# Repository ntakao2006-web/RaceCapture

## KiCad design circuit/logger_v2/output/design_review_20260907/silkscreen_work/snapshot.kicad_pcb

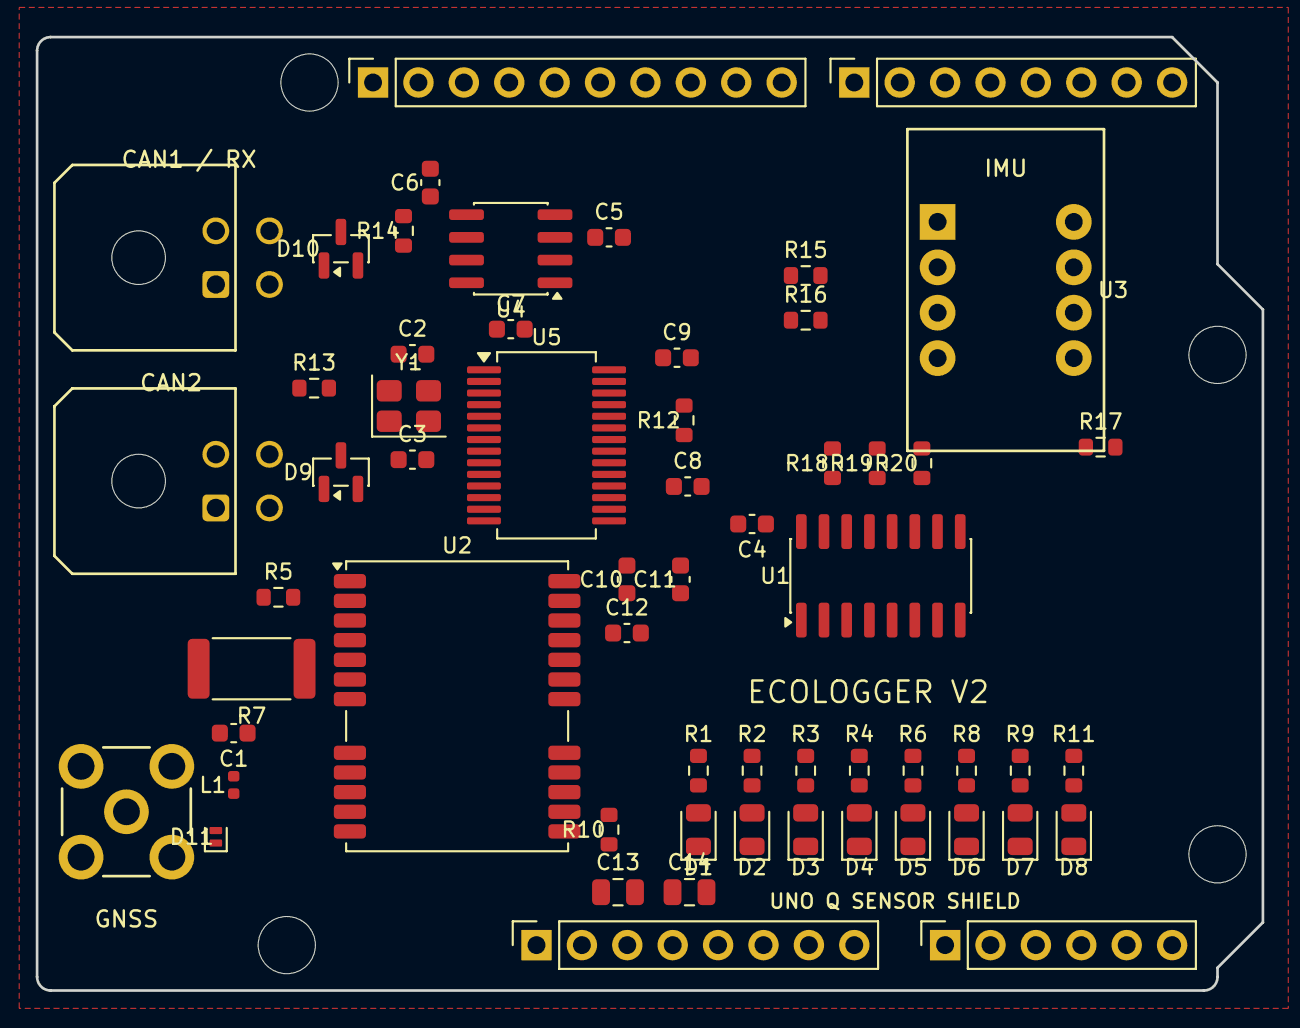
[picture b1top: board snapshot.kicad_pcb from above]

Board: 2 copper layers, 68.6 x 53.3 mm, 63 parts (0 on the bottom side), 46 nets, no tracks yet.

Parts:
C1, C4, C5, C6, C7, C8, C9, C10, C12: 100nF; C_0603_1608Metric
C2, C3: 18pF; C_0603_1608Metric
C11: 1uF; C_0603_1608Metric
C13, C14: 10uF; C_0805_2012Metric
D1, D2, D3, D4, D5, D6, D7, D8: GREEN 0805; LED_0805_2012Metric
D9, D10: NUP2105LT1G; SOT-23
D11: RF ESD; D_SOD-882
J1: S-037-TGG; SMA_S-037-TGG_Horizontal
J2: Digital/PWM; PinSocket_1x10_P2.54mm_Vertical
J3: Power; PinSocket_1x08_P2.54mm_Vertical
J4: Analog; PinSocket_1x06_P2.54mm_Vertical
J5: Digital/PWM; PinSocket_1x08_P2.54mm_Vertical
J6, J7: 43045-0400; Molex_Micro-Fit_3.0_43045-0400_2x02_P3.00mm_Horizontal
L1: 27nH; L_0402_1005Metric
MH1, MH2, MH3, MH4: MountingHole_3.2mm
R1, R2, R3, R4, R6, R8, R9, R11: 680R; R_0603_1608Metric
R5, R10, R12, R17: 10k; R_0603_1608Metric
R7: 22R 1W; R_2512_6332Metric
R13, R14: 120; R_0603_1608Metric
R15, R16: 4.7k; R_0603_1608Metric
R18, R19, R20: 47k; R_0603_1608Metric
U1: 74HC595D,118; SOIC-16_3.9x9.9mm_P1.27mm
U2: NEO-M9N-00B; ublox_NEO
U3: BNO055_module; AE_BNO055_BO
U4: ATA6561-GAQW-N; SOIC-8_3.9x4.9mm_P1.27mm
U5: MCP25625-E/SS; SSOP-28_5.3x10.2mm_P0.65mm
Y1: 20MHz 12pF; Crystal_SMD_3225-4Pin_3.2x2.5mm

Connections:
+3V3: C4.1, C6.1, C7.1, C8.1, C10.1, C11.1, C12.1, C13.1, J3.4, R5.1, R12.1, R15.2, R16.2, R17.1, U1.10, U1.16, U2.22, U2.23, U3.1, U4.1, U4.5, U5.1, U5.19
+5V: C5.1, C9.1, C14.1, J3.5, J6.1, U4.3, U5.27
/CAN1_RXD: J5.3, U4.4
/CAN2_CS_N: J2.8, R12.2, U5.17
/CAN2_INT_N: J2.9, U5.13
/CAN2_RESET_N: J2.10, R17.2, U5.18
/GNSS_PPS: J5.2, U2.3
/GNSS_RESET_N: J5.5, R5.2, U2.8
/GNSS_RF: D11.2, J1.1, L1.1, U2.11
/GNSS_RXD: J5.7, U2.21
/GNSS_TXD: J5.8, U2.20
/IMU_RESET_N: J5.6, U3.5
/IMU_SCL: J2.1, R15.1, U3.4
/IMU_SDA: J2.2, R16.1, U3.3
/SPI2_MISO: J2.6, U5.16
/SPI2_MOSI: J2.7, R18.1, U1.14, U5.15
/SPI2_SCK: J2.5, R19.1, U1.11, U5.14
/STATUS_LATCH: J5.1, R20.1, U1.12
GND: C1.2, C2.2, C3.2, C4.2, C5.2, C6.2, C7.2, C8.2, C9.2, C10.2, C11.2, C12.2, C13.2, C14.2, D1.1, D2.1, D3.1, D4.1, D5.1, D6.1, D7.1, D8.1, D9.3, D10.3, D11.1, J1.2, J2.4, J3.6, J3.7, J6.4, J7.4, R10.2, R18.2, R19.2, R20.2, U1.8, U1.13, U2.7, U2.10, U2.12, U2.13, U2.24, U3.2, U3.7, U4.2, U4.8, U5.5, U5.10, U5.26, Y1.2, Y1.4
unnamed: C1.1, L1.2, R7.2
unnamed: D1.2, R1.2
unnamed: D2.2, R2.2
unnamed: D3.2, R3.2
unnamed: D4.2, R4.2
unnamed: D5.2, R6.2
unnamed: D6.2, R8.2
unnamed: D7.2, R9.2
unnamed: D8.2, R11.2
unnamed: D9.1, J6.2, R13.2, U5.4
unnamed: D9.2, J6.3, R13.1, U5.3
unnamed: D10.1, J7.2, R14.2, U4.7
unnamed: D10.2, J7.3, R14.1, U4.6
unnamed: R1.1, U1.15
unnamed: R2.1, U1.1
unnamed: R3.1, U1.2
unnamed: R4.1, U1.3
unnamed: R6.1, U1.4
unnamed: R8.1, U1.5
unnamed: R9.1, U1.6
unnamed: R11.1, U1.7
unnamed: R10.1, U2.14
unnamed: R7.1, U2.9
unnamed: C2.1, U5.9, Y1.3
unnamed: C3.1, U5.8, Y1.1
unnamed: U5.21, U5.28
unnamed: U5.20, U5.24

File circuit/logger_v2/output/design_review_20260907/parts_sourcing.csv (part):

"Reference","Existing_part","Proposed_part","Manufacturer","LCSC","JLC_library","JLC_assembly","Package","Stock_reported","Stock_evidence","Checked_JST","Status","URL","Notes"
"U1","TC74HC595AF","74HC595D,118","Nexperia","C5947","Basic","Economic and Standard","SOIC-16 3.9mm","302263","JLC indexed page snapshot","2026-09-07","Selected final design","https://jlcpcb.com/partdetail/Nexperia-74HC595D118/C5947","Change footprint from 5.3mm SOP; same logic pinout"
"U2","NEO-M9N-00B","NEO-M9N-00B","u-blox","C5119087","Extended","Standard Only","SMD-24P","500","JLC indexed page snapshot; current page confirms Standard Only","2026-09-07","Selected final design","https://jlcpcb.com/partdetail/UBLOX-NEO_M9N00B/C5119087","LCSC separately showed 322; do not confuse supplier stock with allocated PCBA stock"
"U3","AE-BNO055-BO","AE-BNO055-BO","Akizuki","","Unconfirmed","Excluded from SMT BOM/CPL; post-assembly","18x11mm module","TBD","No exact JLC registration verified","2026-09-07","Selected post-assembly","https://akizukidenshi.com/catalog/g/g116996/","Use module-specific BOM; never assign bare BNO055 C93216 to this footprint"
"U3 alternative","AE-BNO055-BO","BNO055","Bosch Sensortec","C93216","Extended","Standard Only","LGA-28 5.2x3.8mm","8957","JLC category indexed stock snapshot","2026-09-07","Alternative only","https://jlcpcb.com/partdetail/BoschSensortec-BNO055/C93216","Requires full circuit redesign around same sensor IC and axis validation"
"U4","ATA6561-GAQW-N","ATA6561-GAQW","Microchip","C2929602","Extended","SMT listed; service class not displayed","SOIC-8","1117","LCSC stock only; JLC quantity not displayed","2026-09-07","Selected final design","https://jlcpcb.com/partdetail/MicrochipTech-ATA6561GAQW/C2929602","AEC-Q100 version instead of industrial -N; confirm ordering allocation"
"U5","MCP25625T-E/SS","MCP25625-E/SS","Microchip","C184944","Extended","Economic and Standard","SSOP-28 5.3mm","86","JLC indexed page snapshot; indexed 10 months ago","2026-09-07","Selected final design","https://jlcpcb.com/partdetail/MicrochipTech-MCP25625_ESS/C184944","T suffix changes reel packaging; same IC and SSOP; stock must be refreshed at order"
"D1-D8","3mm THT LED","KT-0805G","Hubei KENTO","C2297","Basic","Economic and Standard","0805","1845064","JLC category page indexed today","2026-09-07","Selected final design","https://jlcpcb.com/partdetail/KT-0805G/C2297","Green Vf2.6-3.1V at5mA; selected680ohm resistors; verify actual low-current brightness"
"D9-D10","PEC3824C2A-AU","NUP2105LT1G","onsemi","C14486","Extended","SMT listed","SOT-23","190745","JLC indexed page snapshot","2026-09-07","Selected final design","https://jlcpcb.com/partdetail/NUP2105LT1G/C14486","Pin1/2 line pin3 common; 24V 30pF max; standard part is not SZ automotive-qualified variant"
"D11","new RF ESD","PESD5V0F1BL,315","Nexperia","C45961","Extended","Economic and Standard","SOD882 DFN1006-2","18223","JLC indexed page snapshot","2026-09-07","Selected final design","https://jlcpcb.com/partdetail/Nexperia-PESD5V0F1BL315/C45961","0.4pF typ bidirectional RF ESD; mount at SMA"
"L1","27nH unspecified","LQG15HS27NJ02D","Murata","C12669","Extended","Economic and Standard","0402","InStock quantity unverified","Current JLC structured availability; no quantity displayed","2026-09-07","Selected final design","https://jlcpcb.com/partdetail/LQG15HS27NJ02D/C12669","27nH 350mA DCR0.46ohm SRF1.7GHz; footprint changes from0603"
"L1 alternate","27nH unspecified","LQG15HZ27NH02D","Murata","C237452","Extended","Economic and Standard","0402","1096","JLC indexed page snapshot","2026-09-07","Alternative if allocation unavailable","https://jlcpcb.com/partdetail/MurataElectronics-LQG15HZ27NH0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","27nH 3percent AEC-Q200; confirm RF curve for final selected choke"
"Y1","HUSG-20.000-20","XC2EL89COO-114YLC-20M","YXC","C18213008","Extended","Economic and Standard","SMD3225-4P","4098","JLC indexed page snapshot","2026-09-07","Selected final design","https://jlcpcb.com/partdetail/19387115-XC2EL89COO_114YLC20M/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","20MHz CL12pF ESR70ohm -40to125C; C2/C3 must match12pF load"
"Y1 alternate","HUSG-20.000-20","ABM8G-20.000MHZ-18-D2Y-T","Abracon","C1985763","Extended","Economic and Standard","SMD3225-4P","13","JLC indexed page snapshot; available order qty10","2026-09-07","CL18pF alternative limited stock","https://jlcpcb.com/partdetail/AbraconLLC-ABM8G_20_000MHZ_18_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","20MHz CL18pF ESR80ohm -40to85C"
"J1","S-037-TGG","S-037-TGG","COSMTEC","","Unconfirmed","Excluded from SMT BOM/CPL; post-assembly","Horizontal THT SMA","TBD","No exact JLC registration verified","2026-09-07","Selected post-assembly; orientation fixed","https://akizukidenshi.com/goodsaffix/S-037-TGG_20220729.pdf","Do not substitute generic SMA without comparing manufacturer dimensions and RF launch"
"J2-J5","UNO shield headers","UNO shield stacking headers","TBD","","Unconfirmed","Excluded from SMT BOM/CPL; post-assembly","2.54mm long-tail stacking headers","TBD","Exact manufacturer and part not specified","2026-09-07","Selected post-assembly; orientation fixed","https://docs.arduino.cc/hardware/uno-q/","Sockets alone may not provide required male shield tails; verify stand-off and UNO Q clearance"
"J6-J7","43045-0400","43045-0400","Molex","","Unconfirmed","Excluded from SMT BOM/CPL; post-assembly","Micro-Fit3.0 2x2 horizontal","TBD","No exact JLC registration verified","2026-09-07","Selected post-assembly; orientation fixed","https://www.molex.com/en-us/products/part-detail/430450400","Check exact suffix and board retention features before matching procurement alternates"
"R7 rejected original value","22R 1W","25121WJ0220T4E","UNI-ROYAL","C27258","Extended","Unconfirmed","2512","InStock quantity hidden","Current JLC HTML structured availability; separate LCSC indexed stock86200","2026-09-07","Not selected; insufficient tolerance margin","https://jlcpcb.com/partdetail/28007-25121WJ0220T4E/C27258","22ohm5%1W; 22R nominal does not prove below150mA including tolerances"
"R7","22R 1W","25121WJ0270T4E","UNI-ROYAL","C25478","Extended","Unconfirmed","2512","InStock quantity hidden","Current JLC HTML structured availability","2026-09-07","Selected final design","https://jlcpcb.com/partdetail/C25478","27ohm5%1W; below141mA at3.6V ignoring other resistance but antenna voltage lower by0.10V at20mA"
"C1/C4/C5/C6/C7/C8/C9/C10/C12","100nF or new","CC0603KRX7R9BB104","YAGEO","C14663","Basic","Economic and Standard","0603","65537578","JLC indexed today; available order51319038","2026-09-07","Selected final design","https://jlcpcb.com/partdetail/Yageo-CC0603KRX7R9BB104/C14663","100nF X7R50V10%; C1 RF bias capacitor may share this part"
"C11","new1uF","CL10A105KB8NNNC","Samsung Electro-Mechanics","C15849","Basic","Economic and Standard","0603","9147549","JLC indexed today; available order6454019","2026-09-07","Selected final design","https://jlcpcb.com/partdetail/C15849","1uF X5R50V10%; maximum rated temperature85C"
"C13/C14","new10uF","CL21A106KAYNNNE","Samsung Electro-Mechanics","C15850","Basic","Economic and Standard","0805","7852178","JLC indexed today; available order6491601","2026-09-07","Selected final design","https://jlcpcb.com/partdetail/CL21A106KAYNNNE/C15850","10uF X5R25V10%; account for DC bias; maximum rated temperature85C"
"R18/R19/R20","new47k","0603WAF4702T5E","UNI-ROYAL","C25819","Basic","Economic and Standard","0603","InStock quantity hidden","Current JLC HTML structured availability","2026-09-07","Selected final design","https://jlcpcb.com/partdetail/C25819","47k1%100mW"
"R1/R2/R3/R4/R6/R8/R9/R11","1k","0603WAF6800T5E","UNI-ROYAL","C23228","Basic","Economic and Standard","0603","InStock quantity hidden","Current JLC HTML structured availability","2026-09-07","Selected final design","https://jlcpcb.com/partdetail/0603WAF6800T5E/C23228","680ohm1%100mW; verify actual LED brightness"
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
